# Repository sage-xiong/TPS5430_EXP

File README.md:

# Project description

A learning project to learn about switching power supplies.The Buck chip is a TPS5430DDA.

# Design software

KiCAD v6.0.2

# Circuit performance

## version 1.2

- Fixed the feedback trace under output filter capacitor.

## version 1.1

- Finished the First version layout.

## version 1.4

- For the input, an input filter capacitor is added;
- For the output, a tantalum capacitor and an MLCC are added for filtering;
- Change the fixed output to an adjustable output;

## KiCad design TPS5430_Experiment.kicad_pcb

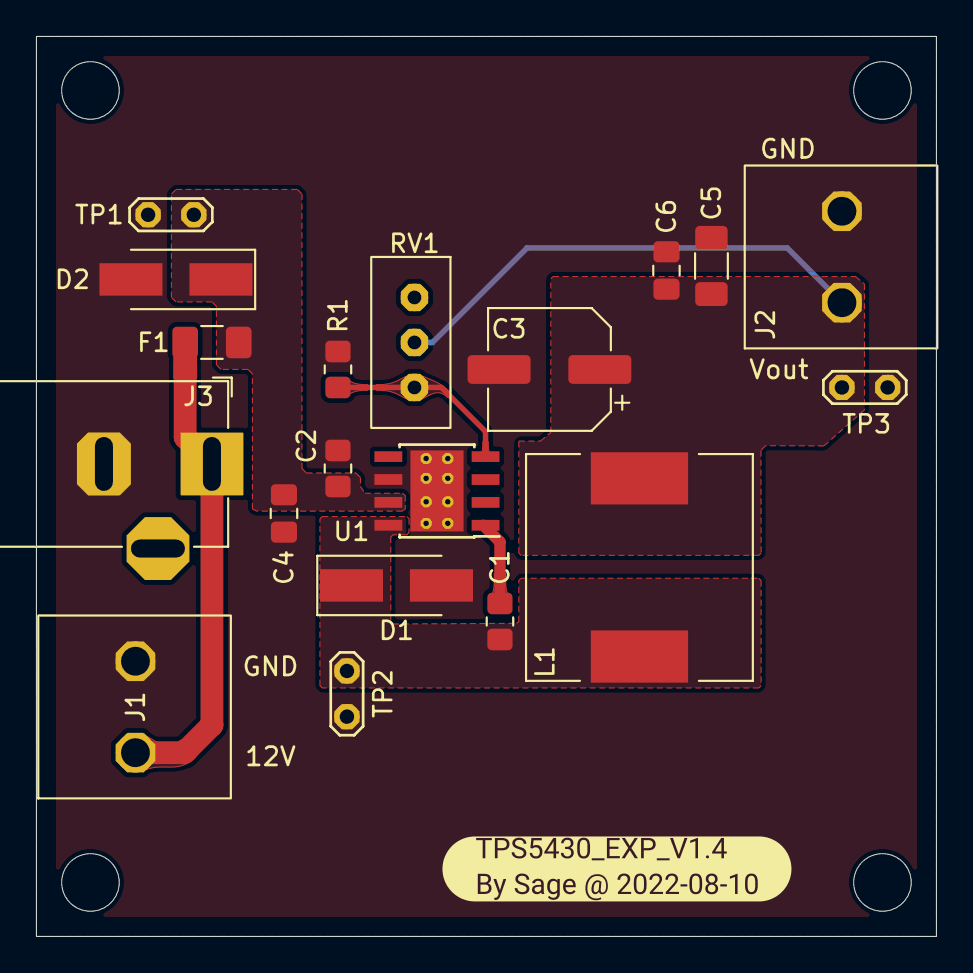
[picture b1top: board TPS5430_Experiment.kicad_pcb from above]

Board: 2 copper layers, 50.0 x 50.0 mm, 20 parts (0 on the bottom side), 7 nets.

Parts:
C1, C2: 10uF/1Ohm; R_0805_2012Metric_Pad1.20x1.40mm_HandSolder
C3: 220uF/35mOhm; CP_Elec_6.3x5.4
C4, C6: 0.1uF; C_0805_2012Metric_Pad1.18x1.45mm_HandSolder
C5: 10uF; C_1206_3216Metric_Pad1.33x1.80mm_HandSolder
D1, D2: SS34; D_SMA_Handsoldering
F1: Fuse; Fuse_1206_3216Metric_Pad1.42x1.75mm_HandSolder
J1, J2: HT5.08; HT5.08-2P
J3: Barrel_Jack; BarrelJack_Horizontal
L1: 22uH/66mOhm; L_12x12mm_H8mm
R1: 10kOhm; R_0805_2012Metric_Pad1.20x1.40mm_HandSolder
RV1: 100kOhm; 3296W
TP1, TP2, TP3: TestPoint; TestPoint_2Pads_Pitch2.54mm_Drill0.8mm
U1: TPS5430DDA; TI_SO-PowerPAD-8_ThermalVias
kibuzzard-62F31943: G***; kibuzzard-62F31943

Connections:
GNDREF: C2.2, C3.2, C4.2, C5.2, C6.2, D1.2 (A), D2.2 (A), J1.2, J2.2, J3.2, R1.2, TP1.2, TP2.2, TP3.2, U1.6 (GND), U1.9 (GNDPAD)
unnamed: C1.1, U1.1 (BOOT)
unnamed: C1.2, D1.1 (K), L1.1, TP2.1, U1.8 (PH)
unnamed: C2.1, C4.1, D2.1 (K), F1.2, TP1.1, U1.7 (VIN)
unnamed: C3.1, C5.1, C6.1, J2.1, L1.2, RV1.2, TP3.1
unnamed: F1.1, J1.1, J3.1
unnamed: R1.1, RV1.3, U1.4 (VSENSE)

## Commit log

2022-08-02 Add Project File
2022-08-02 Add Sch File.
2022-08-02 Add PCB File.
2022-08-02 Add ibom File.
2022-08-02 Add Gerber Files.
2022-08-03 Creat3e README.md
2022-08-03 Create license
2022-08-03 Add README_CN.md
2022-08-04 Add v1.1 images.
2022-08-04 Add v1.2 images
2022-08-04 update the README.md file.
2022-08-22 更新原理图
2022-08-22 Add version 1.4 imagee
